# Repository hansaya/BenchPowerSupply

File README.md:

# This repo contains all the files I used to create the DIY Bench Power Supply.

# For more information https://www.youtube.com/watch?v=PlHGyIHwtQw

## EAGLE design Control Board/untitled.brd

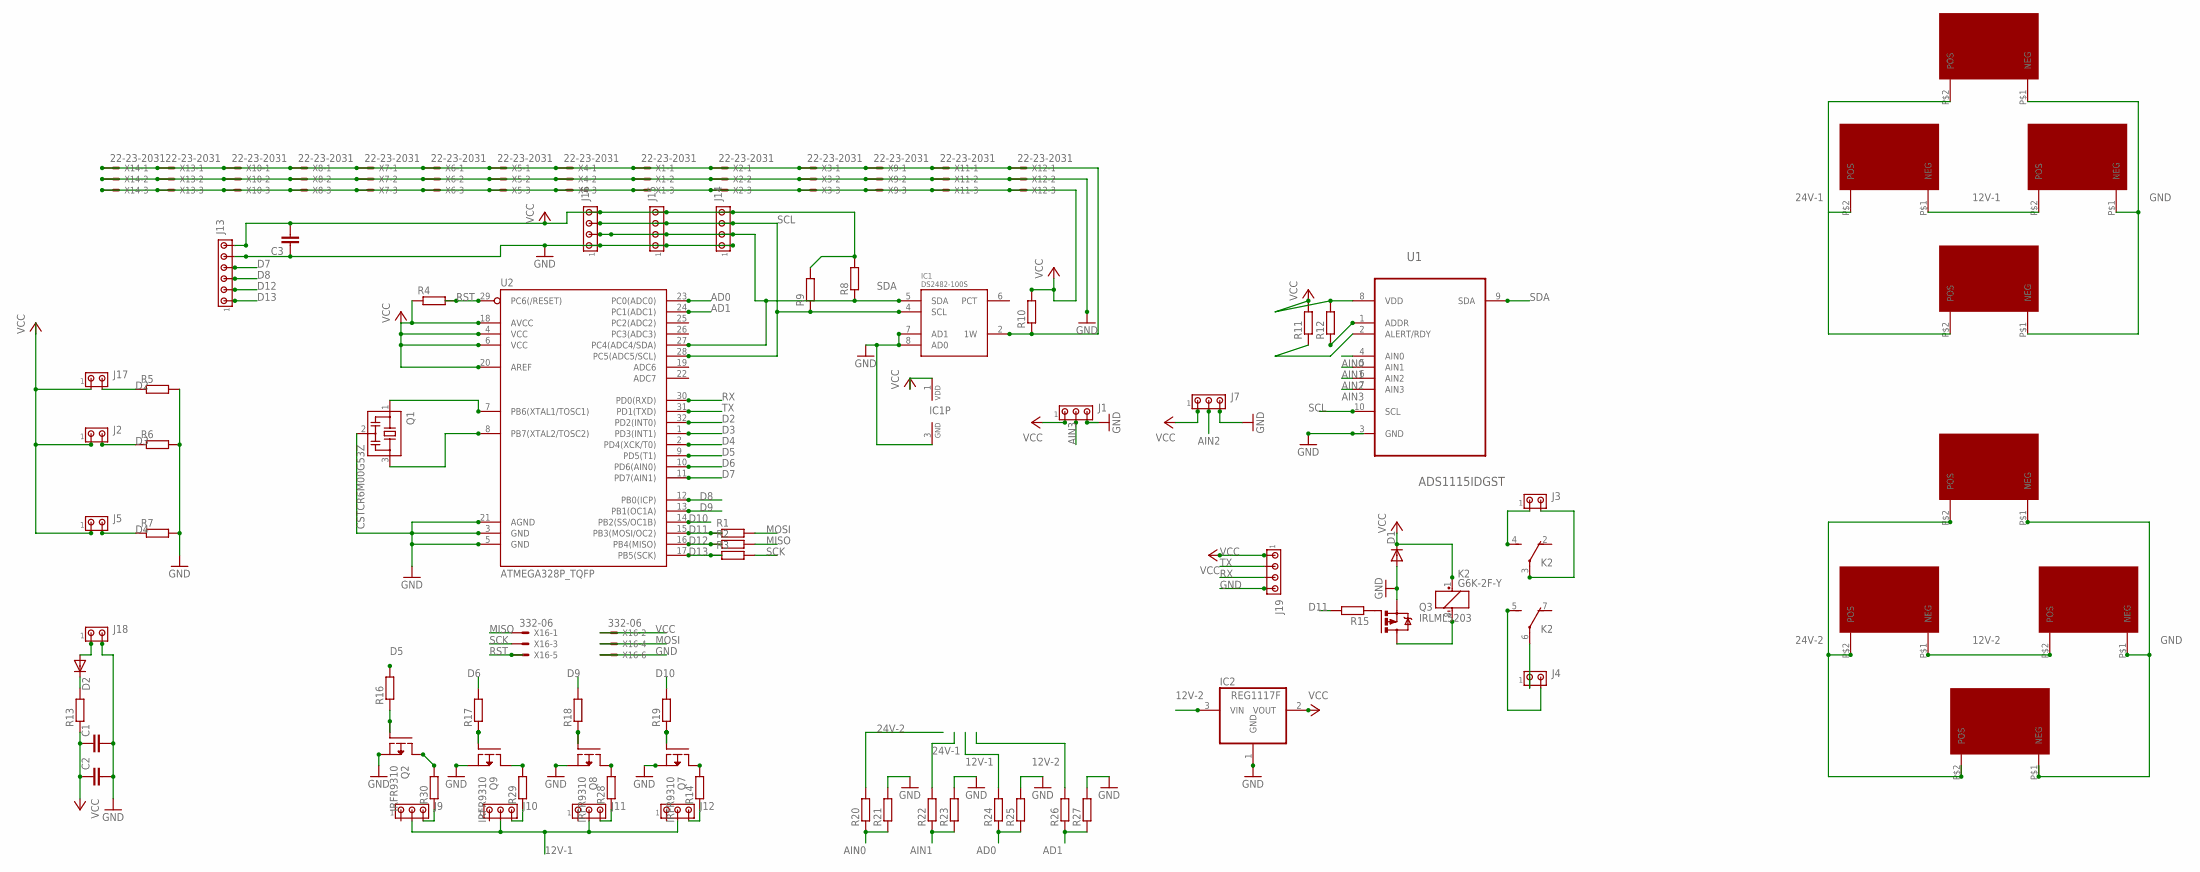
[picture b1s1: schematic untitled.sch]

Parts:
C1, C2, C3: CC1206; C1206
D1, D2: DIODE-DO214AA; DO214AA
IC1: DS2482-100S; SO08
IC2: REG1117F; DD-3
J1, J7, J9, J10, J11, J12: MTA03-100; 10X03MTA
J2, J3, J4, J5, J17, J18: MTA02-100; 10X02MTA
J13: MTA06-100; 10X06MTA
J14, J15, J16, J19: MTA04-100; 10X04MTA
K2: G6K-2F-Y
Q1: CSTCR6M00G53Z; CSTCR6M
Q2, Q7, Q8, Q9: IRFR9310; TO252
Q3: IRLML5203; MICRO3
R1, R2, R3, R4, R5, R6, R7, R8, R9, R10, R11, R12, R15, R16, R17, R18, R19, R20, R21, R22, R23, R24, R25, R26, R27: R-EU_R0603; R0603
R13: RR2010; R2010
R14, R28, R29, R30: R-EU_M1206; M1206
U1: ADS1115IDGST; SOP50P490X110-10N
U2: ATMEGA328P_TQFP; TQFP32-08
U$1, U$2, U$3, U$4, U$5, U$6, U$7, U$8: XT60
X1, X2, X3, X4, X5, X6, X7, X8, X9, X10, X11, X12, X13, X14: 22-23-2031
X16: 332-06

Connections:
12V-1: J9.2, J10.2, J11.2, J12.2, R24.2, U$1.P$1 (NEG), U$2.P$2 (POS)
12V-2: IC2.3 (VIN), R26.2, U$6.P$1 (NEG), U$7.P$2 (POS)
24V-1: R22.2, U$1.P$2 (POS), U$3.P$2 (POS), U$4.P$2 (POS)
24V-2: R20.2, U$5.P$2 (POS), U$6.P$2 (POS), U$8.P$2 (POS)
AD0: R24.1, R25.1, U2.23 (PC0(ADC0))
AD1: R26.1, R27.1, U2.24 (PC1(ADC1))
AIN0: R20.1, R21.1, U1.4 (AIN0)
AIN1: R22.1, R23.1, U1.5 (AIN1)
AIN2: J7.2, U1.6 (AIN2)
AIN3: J1.2, U1.7 (AIN3)
D2: J17.2, R5.1, U2.32 (PD2(INT0))
D3: J2.2, R6.1, U2.1 (PD3(INT1))
D4: J5.2, R7.1, U2.2 (PD4(XCK/T0))
D5: R16.2, U2.9 (PD5(T1))
D6: R17.2, U2.10 (PD6(AIN0))
D7: J13.4, U2.11 (PD7(AIN1))
D8: J13.3, U2.12 (PB0(ICP))
D9: R18.2, U2.13 (PB1(OC1A))
D10: R19.2, U2.14 (PB2(SS/OC1B))
D11: R1.1, R15.2, U2.15 (PB3(MOSI/OC2))
D12: J13.2, R2.1, U2.16 (PB4(MISO))
D13: J13.1, R3.1, U2.17 (PB5(SCK))
GND: C1.2, C2.2, C3.1, D1.A, IC1.3 (GND), IC1.7 (AD1), IC1.8 (AD0), IC2.1 (GND), J1.3, J7.3, J13.5, J14.1, J15.1, J16.1, J18.2, J19.4, Q1.2, Q2.2 (S), Q3.2 (S), Q7.2 (S), Q8.2 (S), Q9.2 (S), R5.2, R6.2, R7.2, R21.2, R23.2, R25.2, R27.2, U1.3 (GND), U2.3 (GND), U2.5 (GND), U2.21 (AGND), U$2.P$1 (NEG), U$3.P$1 (NEG), U$4.P$1 (NEG), U$5.P$1 (NEG), U$7.P$1 (NEG), U$8.P$1 (NEG), X1.2, X2.2, X3.2, X4.2, X5.2, X6.2, X7.2, X8.2, X9.2, X10.2, X11.2, X12.2, X13.2, X14.2, X16.6
MISO: R2.2, X16.1
MOSI: R1.2, X16.4
unnamed: IC1.2 (1W), R10.1, X1.1, X2.1, X3.1, X4.1, X5.1, X6.1, X7.1, X8.1, X9.1, X10.1, X11.1, X12.1, X13.1, X14.1
unnamed: Q1.1, U2.7 (PB6(XTAL1/TOSC1))
unnamed: Q1.3, U2.8 (PB7(XTAL2/TOSC2))
unnamed: J9.3, R30.1
unnamed: Q3.1 (G), R15.1
unnamed: K2.8 (-), Q3.3 (D)
unnamed: Q9.3 (D), R29.2
unnamed: Q2.3 (D), R30.2
unnamed: Q8.3 (D), R28.2
unnamed: Q7.3 (D), R14.2
unnamed: R12.1, U1.1 (ADDR)
unnamed: J3.1, K2.4 (S)
unnamed: R11.1, U1.2 (ALERT/RDY)
unnamed: J10.3, R29.1
unnamed: J11.3, R28.1
unnamed: J12.3, R14.1
unnamed: J3.2, K2.3
unnamed: J4.1, K2.6
unnamed: J4.2, K2.5 (S)
unnamed: D2.A, J18.1
unnamed: D2.C, R13.2
unnamed: Q2.1 (G), R16.1
unnamed: Q9.1 (G), R17.1
unnamed: Q8.1 (G), R18.1
unnamed: Q7.1 (G), R19.1
RST: R4.2, U2.29 (PC6(/RESET)), X16.5
RX: J19.3, U2.30 (PD0(RXD))
SCK: R3.2, X16.3
SCL: IC1.4 (SCL), J14.3, J15.3, J16.3, R9.1, U1.10 (SCL), U2.28 (PC5(ADC5/SCL))
SDA: IC1.5 (SDA), J14.2, J15.2, J16.2, R8.1, U1.9 (SDA), U2.27 (PC4(ADC4/SDA))
TX: J19.2, U2.31 (PD1(TXD))
VCC: C1.1, C2.1, C3.2, D1.C, IC1.1 (VDD), IC2.2 (VOUT), J1.1, J2.1, J5.1, J7.1, J13.6, J14.4, J15.4, J16.4, J17.1, J19.1, K2.1 (+), R4.1, R8.2, R9.2, R10.2, R11.2, R12.2, R13.1, U1.8 (VDD), U2.4 (VCC), U2.6 (VCC), U2.18 (AVCC), U2.20 (AREF), X1.3, X2.3, X3.3, X4.3, X5.3, X6.3, X7.3, X8.3, X9.3, X10.3, X11.3, X12.3, X13.3, X14.3, X16.2

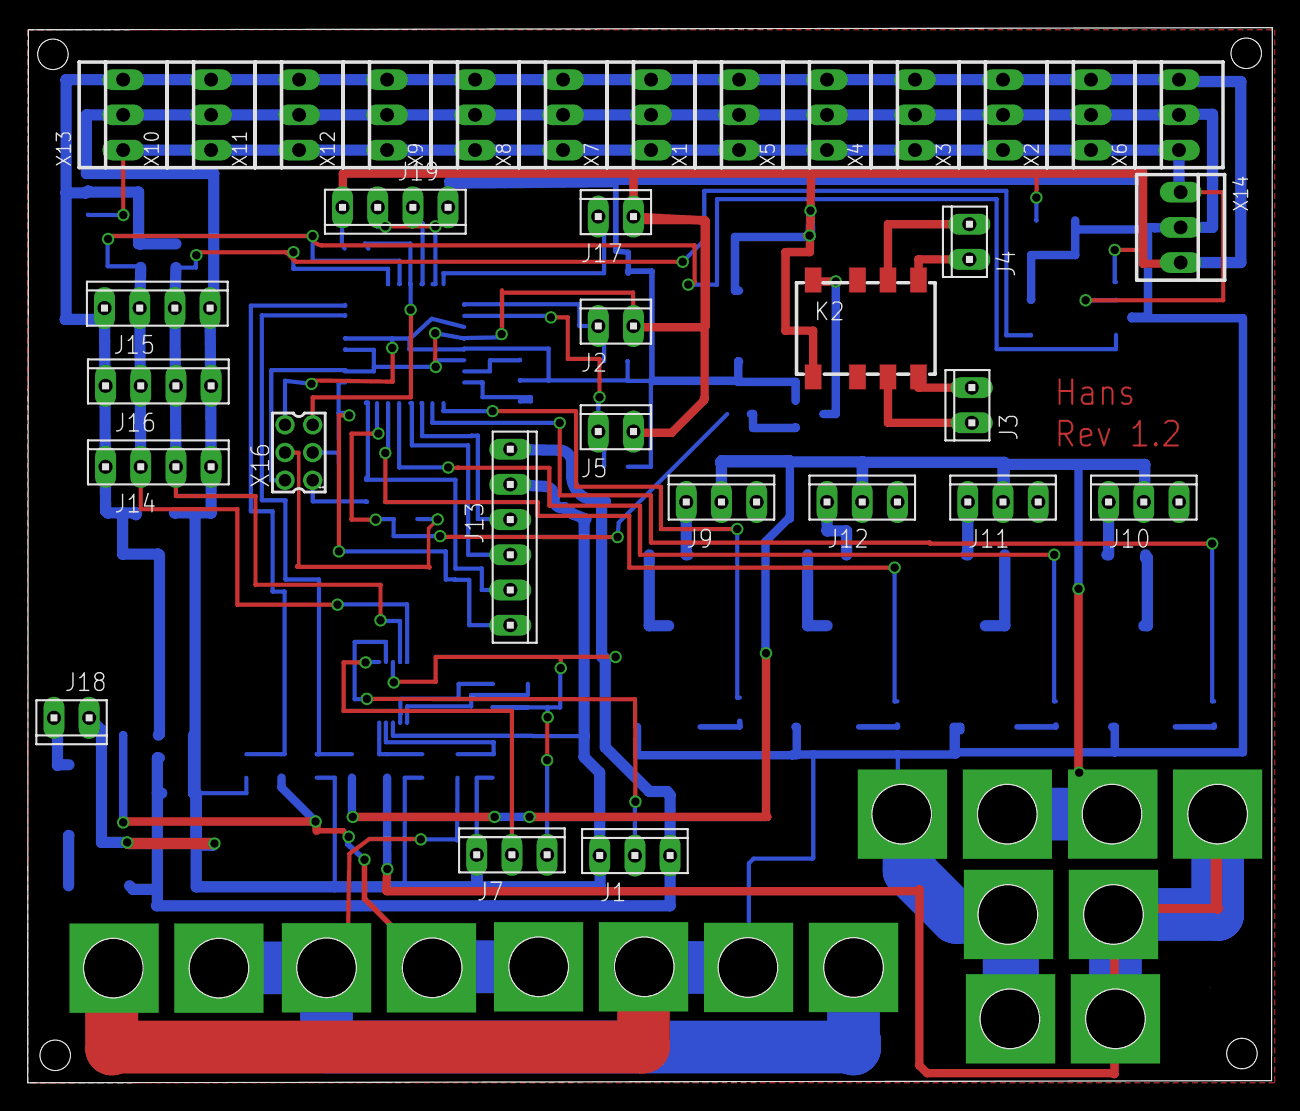
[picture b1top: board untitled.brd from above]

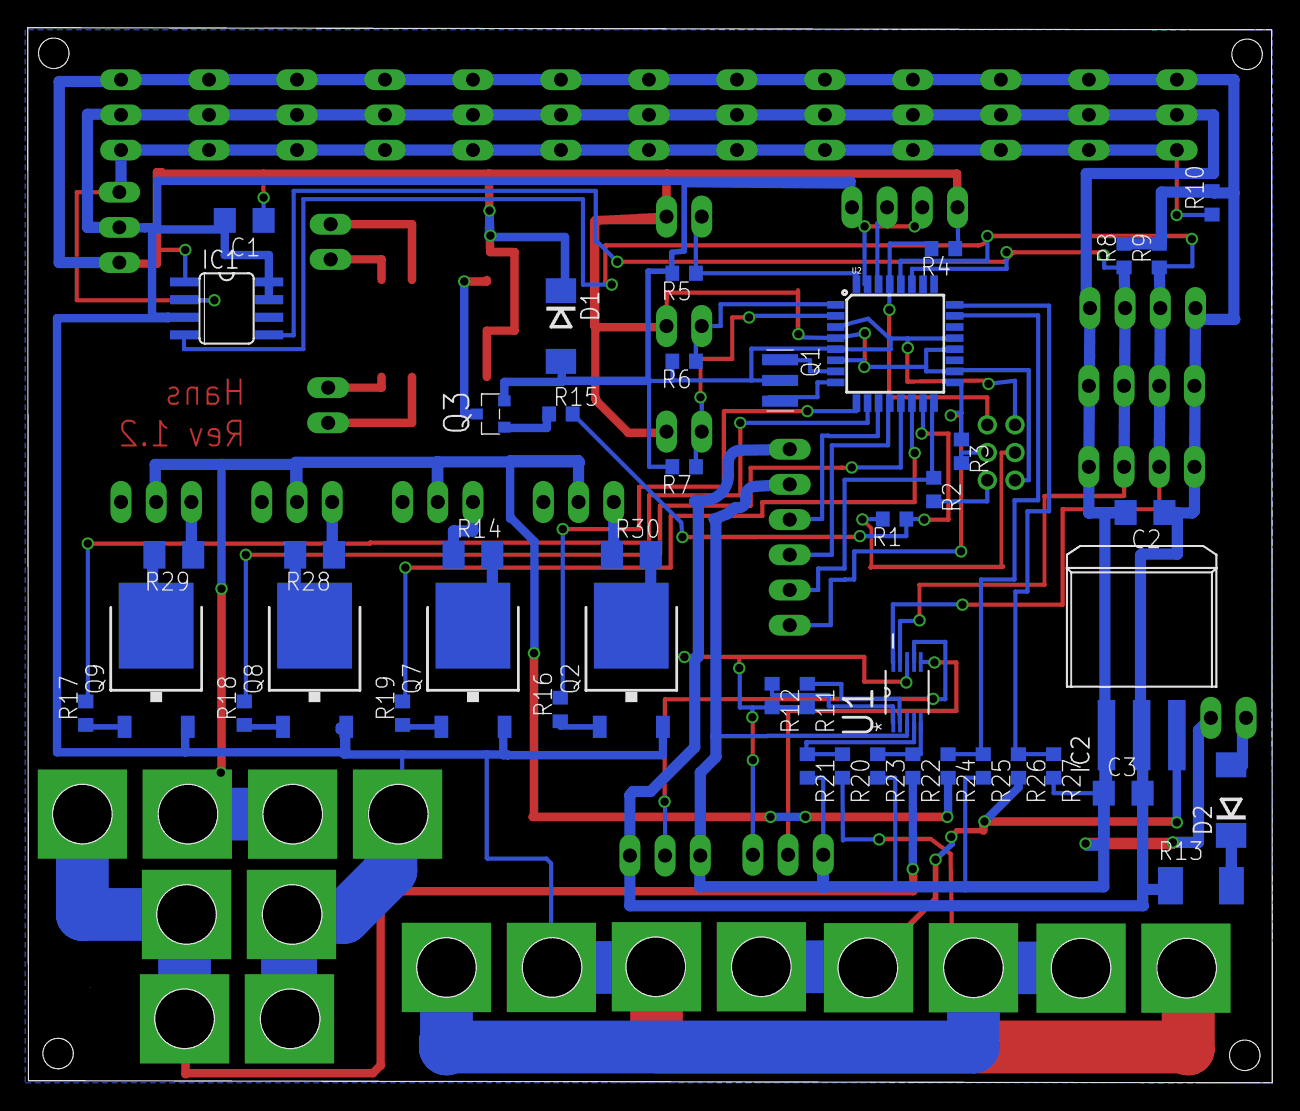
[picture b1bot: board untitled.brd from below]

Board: 2 copper layers, 89.8 x 76.1 mm, 86 parts (45 on the bottom side), 57 nets.

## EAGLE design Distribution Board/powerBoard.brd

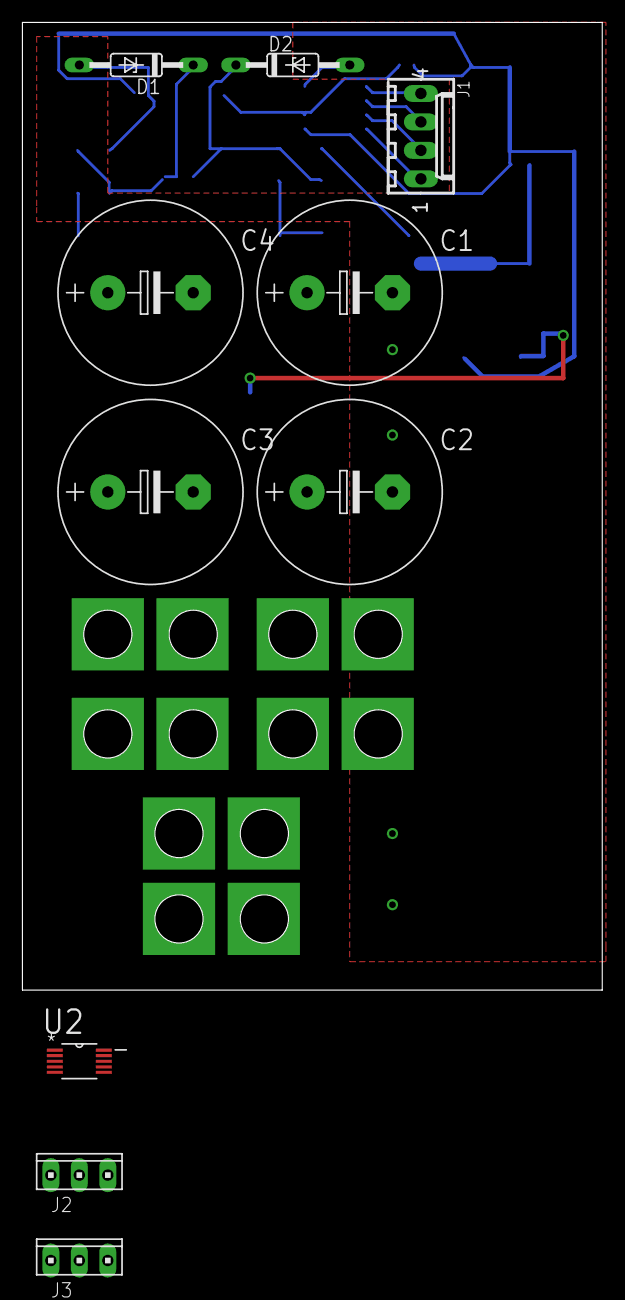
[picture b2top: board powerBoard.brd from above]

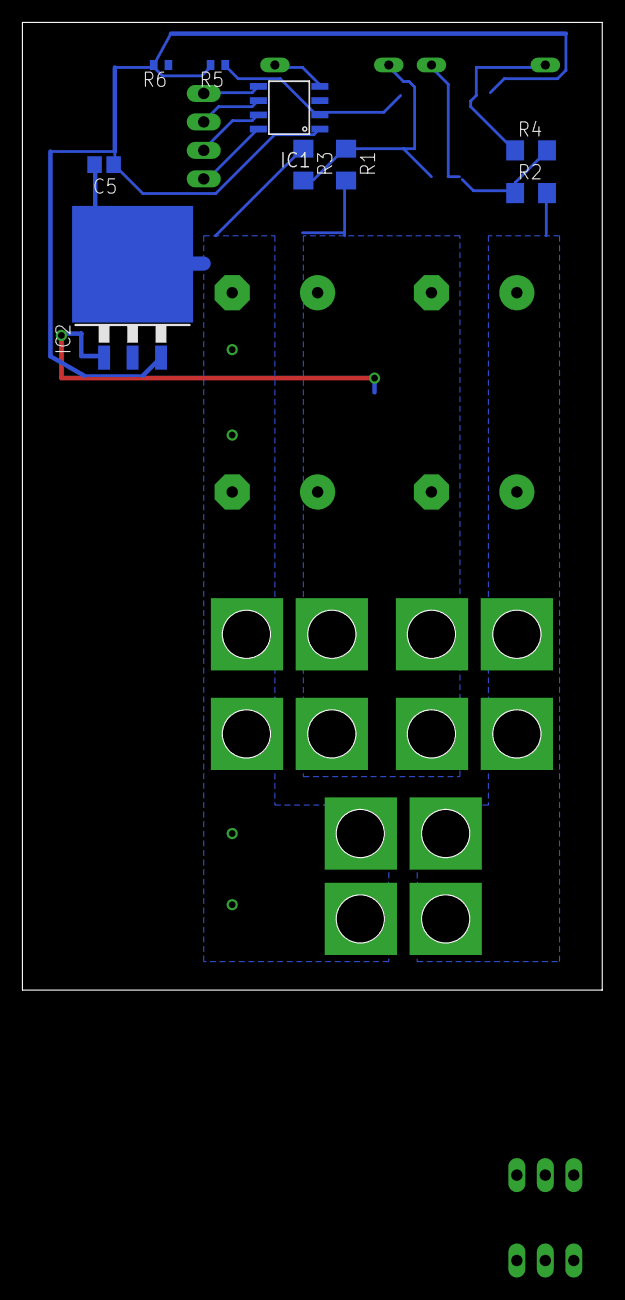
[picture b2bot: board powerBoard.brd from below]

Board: 2 copper layers, 51.7 x 86.3 mm, 25 parts (9 on the bottom side), 14 nets.

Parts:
C1, C2, C3, C4: E7,5-16
C5: C2012
D1, D2: 1N821; DO35Z10
IC1: ADUM1250; SO8-COOL
IC2: LM340S-12; TO263-3
J1: 22-27-2041-04; 6410-04
J2, J3: 10X03MTA
R1, R2, R3, R4: R1206
R5, R6: R1005
U2: ADS1115IDGST; SOP50P490X110-10N
U$1, U$2, U$3, U$4, U$5, U$6: XT60

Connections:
GND: C1.-, C2.-, C5.2, D1.A, D2.A, IC1.4, IC2.TAB, J2.3, J3.3, R3.1, R4.1, U2.3, U$1.P$1, U$4.P$1, U$5.P$1, U$6.P$1
GND2: IC1.5, J1.4
MID: C1.+, C2.+, C3.-, C4.-, IC2.1, R1.2, U$1.P$2, U$2.P$1, U$3.P$1, U$4.P$2
unnamed: J2.1, U2.4
unnamed: J3.1, U2.5
unnamed: IC1.3, R6.1, U2.10
unnamed: D1.C, R2.1, R4.2, U2.6
unnamed: IC1.2, R5.1, U2.9
unnamed: IC1.7, J1.2
unnamed: IC1.6, J1.3
unnamed: D2.C, R1.1, R3.2, U2.7
POS: C3.+, C4.+, R2.2, U$2.P$2, U$3.P$2, U$5.P$2, U$6.P$2
VDD1: C5.1, IC1.1, IC2.3, J2.2, J3.2, R5.2, R6.2, U2.8
VDD2: IC1.8, J1.1

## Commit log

2016-10-05 Init commit
2016-10-05 Cad files for the enclosure

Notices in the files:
parts and their libraries:
SparkFun-DigitalIC: Licensing: Creative Commons ShareAlike 4.0 International - https://creativecommons.org/licenses/by-sa/4.0
